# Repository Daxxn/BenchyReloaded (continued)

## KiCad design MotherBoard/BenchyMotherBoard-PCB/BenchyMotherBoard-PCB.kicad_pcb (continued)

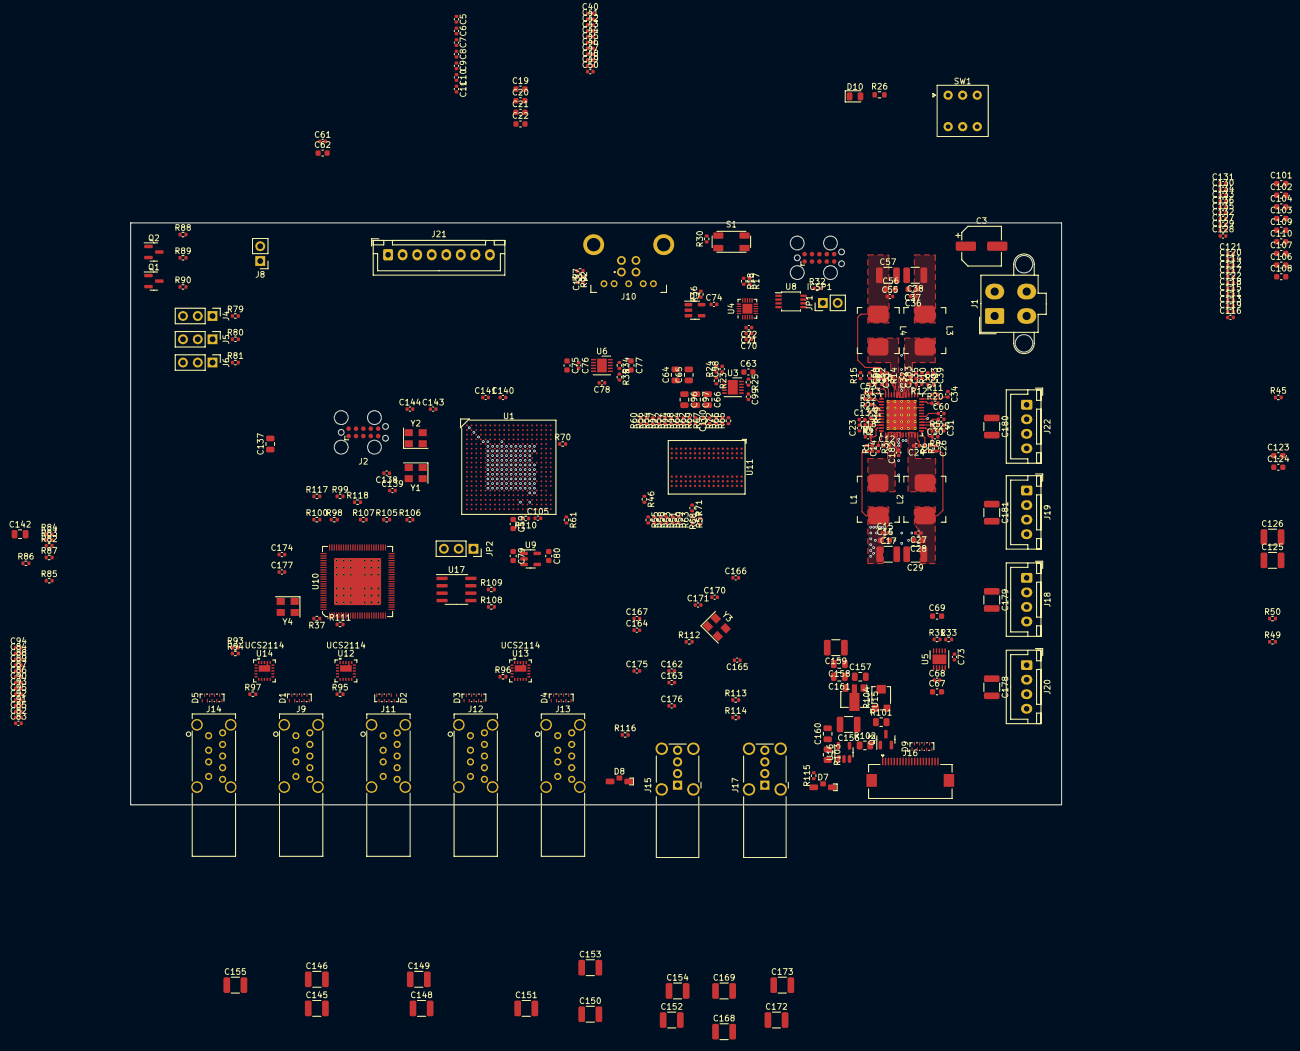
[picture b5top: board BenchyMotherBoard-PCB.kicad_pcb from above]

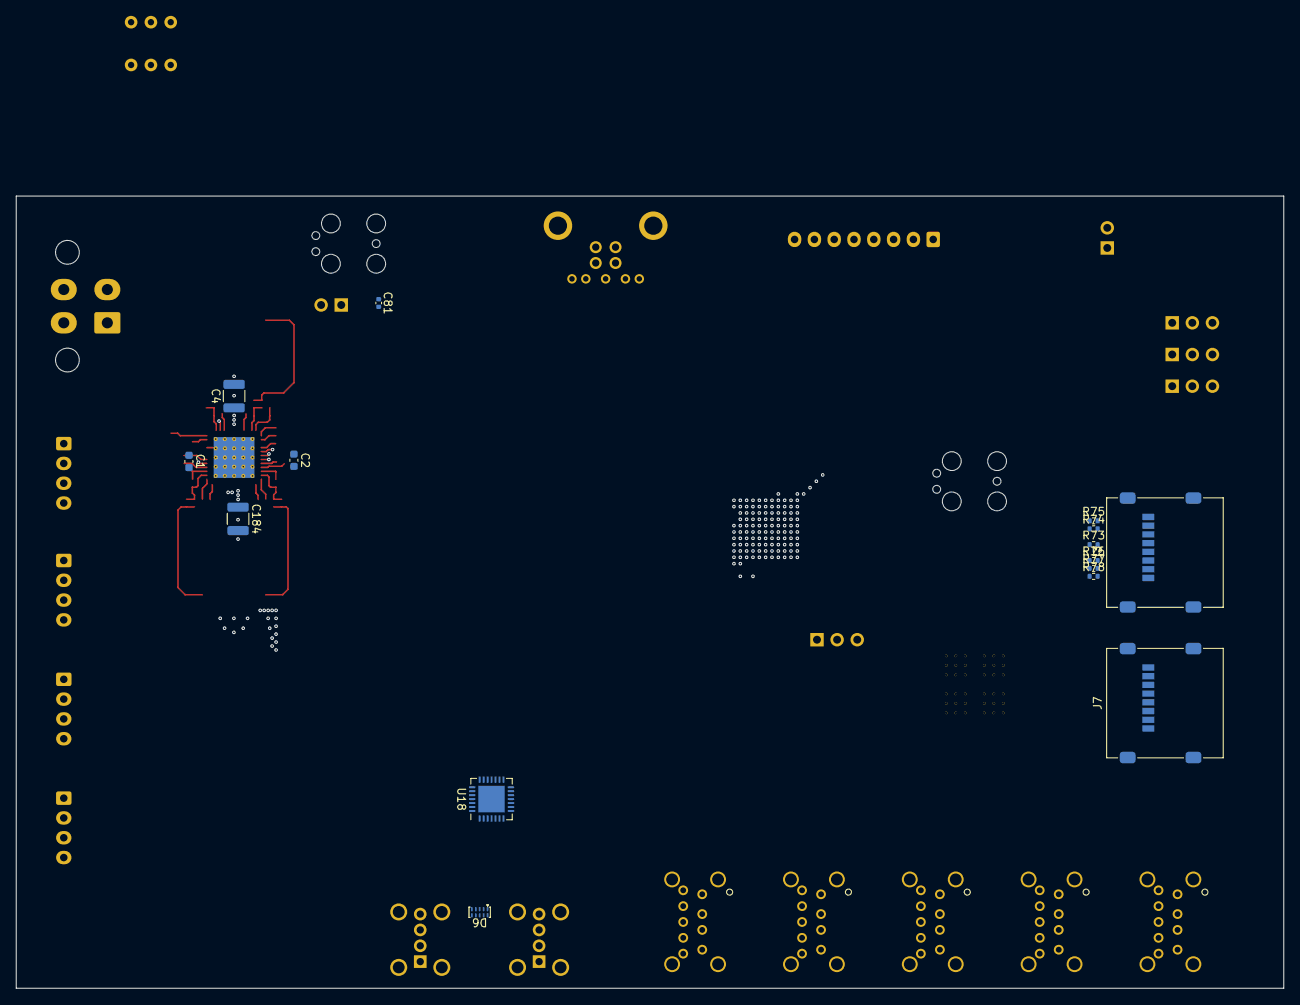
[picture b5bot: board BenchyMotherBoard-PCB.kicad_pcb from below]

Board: 8 copper layers, 160.0 x 100.0 mm, 360 parts (15 on the bottom side), 267 nets.

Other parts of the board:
kibuzzard-63F3F2E0: G***; kibuzzard-63F3F2E0

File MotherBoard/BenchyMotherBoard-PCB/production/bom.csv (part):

Designator,Footprint,Quantity,Value,LCSC Part #
C1,0603,1,100nF,
C10,0402,1,100nF,
C100,0402,1,100nF,
C101,0402,1,100nF,
C102,0402,1,100nF,
C103,0402,1,100nF,
C104,0402,1,100nF,
C105,0402,1,100nF,
C106,0402,1,100nF,
C107,0402,1,100nF,
C108,0402,1,100nF,
C109,0402,1,100nF,
C11,0402,1,100nF,
C110,0402,1,100nF,
C111,0402,1,100nF,
C112,0402,1,100nF,
C113,0402,1,100nF,
C114,0402,1,100nF,
C115,0402,1,100nF,
C116,0402,1,100nF,
C117,0402,1,100nF,
C118,0402,1,100nF,
C119,0402,1,100nF,
C12,0402,1,100nF,
C120,0402,1,100nF,
C121,0402,1,100nF,
C122,0402,1,100nF,
C123,0603,1,1uF,
C124,0603,1,1uF,
C125,1210,1,22uF,
C126,1210,1,22uF,
C127,0402,1,100nF,
C128,0402,1,100nF,
C129,0402,1,100nF,
C13,0402,1,100nF,
C130,0402,1,100nF,
C131,0402,1,100nF,
C132,0402,1,100nF,
C133,0402,1,100nF,
C134,0402,1,100nF,
C135,0402,1,100nF,
C136,0402,1,100nF,
C137,0805,1,4.7uF,
C138,0402,1,15pF,
C139,0402,1,15pF,
C14,0402,1,100nF,
C140,0402,1,1nF,
C141,0402,1,10nF,
C142,0805,1,4.7uF,
C143,0402,1,15pF,
C144,0402,1,15pF,
C145,1210,1,10uF,
C146,1210,1,10uF,
C147,0402,1,100nF,
C148,1210,1,10uF,
C149,1210,1,10uF,
C15,0402,1,100nF,
C150,1210,1,10uF,
C151,1210,1,10uF,
C152,1210,1,10uF,
C153,1210,1,10uF,
C154,1210,1,10uF,
C155,1210,1,10uF,
C156,1210,1,10uF,
C157,0805,1,1uF,
C158,0805,1,1uF,
C159,1210,1,10uF,
C16,0603,1,1uF,
C160,0805,1,1uF,
C161,0805,1,100nF,
C162,0402,1,100nF,
C163,0402,1,100nF,
C164,0402,1,100nF,
C165,0402,1,100nF,
C166,0402,1,100nF,
C167,0402,1,100nF,
C168,1210,1,10uF,
C169,1210,1,1uF,
C17,1210,1,10uF,
C170,0402,1,15pF,
C171,0402,1,15pF,
C172,1210,1,10uF,
C173,1210,1,1uF,
C174,0402,1,15pF,
C175,0402,1,100nF,
C176,0402,1,100nF,
C177,0402,1,15pF,
C178,1210,1,10uF,
C179,1210,1,10uF,
C18,0402,1,47pF,
C180,1210,1,10uF,
C181,1210,1,10uF,
C182,0402,1,100nF,
C183,0402,1,100nF,
C184,1210,1,10uF,
C185,0402,1,100nF,
C186,0402,1,100nF,
C187,0402,1,100nF,
C188,0402,1,100nF,
C189,0402,1,100nF,
C19,0603,1,1uF,
C190,0402,1,100nF,
C191,0402,1,100nF,
C192,0402,1,100nF,
C193,0402,1,100nF,
C194,0603,1,1uF,
C195,0402,1,100nF,
C2,0603,1,100nF,
C20,0603,1,1uF,
C21,0603,1,1uF,
C22,0603,1,1uF,
C23,0402,1,330pF,
C24,0402,1,100nF,
C25,0402,1,100nF,
C26,0402,1,100nF,
C27,0402,1,100nF,
C28,0603,1,1uF,
C29,1210,1,10uF,
C3,CP_Elec_6.3x7.7,1,47uF,
C30,0402,1,117pF,
C31,0402,1,1nF,
C32,0402,1,100nF,
C33,0402,1,100pF,
C34,0402,1,100nF,
C35,0402,1,100nF,
C36,0402,1,100nF,
C37,0603,1,1uF,
C38,1210,1,10uF,
C39,0402,1,820pF,
C4,1210,1,10uF,
C40,0402,1,100nF,
C41,0402,1,100nF,
C42,0402,1,100nF,
C43,0402,1,100nF,
C44,0402,1,100nF,
C45,0402,1,100nF,
C46,0402,1,100nF,
C47,0402,1,100nF,
C48,0402,1,100nF,
C49,0402,1,100nF,
C5,0402,1,100nF,
C50,0402,1,100nF,
C51,0402,1,100nF,
C52,0402,1,150pF,
C53,0402,1,100nF,
C54,0402,1,100nF,
C55,0402,1,100nF,
C56,0603,1,1uF,
C57,1210,1,10uF,
C58,0402,1,1.5nF,
C59,0603,1,2.2uF,
C6,0402,1,100nF,
C60,0402,1,100nF,
C61,0603,1,2.2uF,
C62,0603,1,1uF,
C63,0603,1,4.7uF,
C64,0805,1,10uF,
C65,0805,1,10uF,
C66,0805,1,10uF,
C67,0402,1,100nF,
C68,0402,1,100nF,
C69,0603,1,2.2uF,
C7,0402,1,100nF,
C70,0603,1,1uF,
C71,0402,1,100nF,
C72,0402,1,100nF,
C73,0603,1,1uF,
C74,0402,1,100nF,
C75,0603,1,1uF,
C76,0402,1,100nF,
C77,0603,1,4.7uF,
C78,0402,1,200nF,
C79,0603,1,1uF,
C8,0402,1,100nF,
C80,0603,1,1uF,
C81,0402,1,100nF,
C82,0402,1,100nF,
C83,0402,1,100nF,
C84,0402,1,100nF,
C85,0402,1,100nF,
C86,0402,1,100nF,
C87,0402,1,100nF,
C88,0402,1,100nF,
C89,0402,1,100nF,
C9,0402,1,100nF,
C90,0402,1,100nF,
C91,0402,1,100nF,
C92,0402,1,100nF,
C93,0402,1,100nF,
C94,0402,1,100nF,
C95,0402,1,100nF,
C96,0805,1,10uF,
C97,0805,1,10uF,
C98,0402,1,1nF,
C99,0402,1,100nF,
"D1, D2, D3, D4, D5, D9",U-DFN3810-9,6,ESDLC5V0PB8,
D10,0805,1,GREEN,
D11,0805,1,RED,
D12,0805,1,ORANGE,
D13,0805,1,RED,
D14,0805,1,ORANGE,
D15,0805,1,GREEN,
D6,DFN2510A-10,1,PUSB3AB4-2USB,
D7,LED-SMD-1204_RA,1,ORANGE,
D8,LED-SMD-1204_RA,1,YELLOW,
"H1, H2, H3, H4",MountingHole_3.5mm_Pad_Via,4,M3,
"H10, H5, H6, H7, H8, H9",MountingHole_2.2mm_M2_ISO7380_Pad,6,M2,
ICSP1,Tag-Connect_TC2050-IDC-FP_2x05_P1.27mm_Vertical,1,ICSP,
J1,4-Pin_Molex_Mini-Fit_Jr_Vertical_Mount,1,PWR-CONN,
J10,USB-GSB3211311WEU,1,USB3_B,
J11,GSB4116341HR,1,USB3-PORT2,
J12,GSB4116341HR,1,USB3-PORT3,
J13,GSB4116341HR,1,USB3-PORT4,
J14,GSB4116341HR,1,USB3-PORT5,
J15,1002-014-01000,1,USB-INTERNAL-PORT1,
J16,FH12A-20S-0.5SH55,1,TFT-DISPLAY,
J17,1002-014-01000,1,USB-INTERNAL-PORT2,
J18,JST_XH_B4B-XH-A_Vertical,1,COMMS-PWR,
J19,JST_XH_B4B-XH-A_Vertical,1,COMMS-ELOAD,
J2,Tag-Connect_TC2050-IDC-FP_2x05_P1.27mm_Vertical,1,SWD-TAG,
J20,JST_XH_B4B-XH-A_Vertical,1,COMMS-SWITCHER,
J21,JST_XH_B8B-XH-A_1x08_P2.50mm_Vertical,1,RELAYS-CONN,
J22,JST_XH_B4B-XH-A_Vertical,1,COMMS-LOGIC,
J3,microSD_HC_Molex_47219-2001,1,FILES-SD-CARD,
J7,microSD_HC_Molex_47219-2001,1,BOOT-SD-CARD,
J8,PinHeader_1x02_P2.54mm_Vertical,1,FAN-CONN,
J9,GSB4116341HR,1,USB3-PORT1,
JP1,PinHeader_1x02_P2.54mm_Vertical,1,PWR-ICSP-RST,
JP2,PinSocket_1x03_P2.54mm_Vertical,1,WP-JMP,
L1,PA4341,1,22uH,
"L2, L3, L4",PA4341,3,10uH,
Q1,SOT-23,1,SQ2310ES_SOT23,
Q2,SOT-23,1,MMBT2222A,
Q3,SOT-23,1,RQ5A030AP,
R1,0402,1,24K,
R10,0402,1,13K,
R100,0402,1,10K,
R101,0805,1,10 1%,
R102,0805,1,120,
R103,0805,1,330,
R104,Bourns_TC33X,1,10K,
R105,0402,1,10K,
R106,0402,1,200K,
R107,0402,1,200K,
R108,0402,1,2.2K,
R109,0402,1,2.2K,
R11,0402,1,10K,
R110,0402,1,3K,
R111,0402,1,10K,
R112,0402,1,12K 1%,
R113,0402,1,50K,
R114,0402,1,50K,
R115,0402,1,1K,
R116,0402,1,1K,
R117,0402,1,10K,
R118,0402,1,200K,
R119,0402,1,4.7K,
R12,0402,1,15K,
R13,0402,1,8.2K,
R14,0402,1,4.3K,
R15,0402,1,10K,
R16,0402,1,11K,
R17,0402,1,2.2K,
R18,0402,1,2.2K,
R19,0402,1,10K,
R2,0402,1,24K,
R20,0402,1,10K,
R21,0402,1,160K,
R22,0402,1,160K,
R23,0402,1,10K,
R24,0402,1,10K,
R25,0402,1,10K,
R26,0603,1,500,
R27,0402,1,1K,
R28,0402,1,1K,
R29,0402,1,1K,
R3,0402,1,10K,
R30,0402,1,10K,
R31,0603,1,500,
R32,0402,1,10K,
R33,0603,1,500,
R34,0402,1,10K,
R35,0402,1,6.8K,
R36,0402,1,1K,
R37,0402,1,12K 1%,
R38,0603,1,500,
R39,0603,1,500,
R4,0402,1,7.5K,
R40,0603,1,500,
R41,0402,1,10K,
R42,0402,1,100,
R43,0402,1,10K,
R44,0402,1,56,
R45,0402,1,100,
R46,0402,1,56,
R47,0402,1,56,
R48,0402,1,56,
R49,0402,1,10K,
R5,0402,1,10K,
R50,0402,1,10K,
R51,0402,1,56,
R52,0402,1,56,
R53,0402,1,56,
R54,0402,1,56,
R55,0402,1,56,
R56,0402,1,56,
R57,0402,1,56,
R58,0402,1,56,
R59,0402,1,56,
R6,0402,1,6.2K,
R60,0402,1,56,
R61,0402,1,56,
R62,0402,1,56,
R63,0402,1,56,
R64,0402,1,56,
R65,0402,1,56,
R66,0402,1,56,
R67,0402,1,56,
R68,0402,1,56,
R69,0402,1,56,
R7,0402,1,10K,
R70,0402,1,240 1%,
R71,0402,1,240 1%,
R72,0402,1,56,
R73,0402,1,10K,
R74,0402,1,47K,
R75,0402,1,47K,
R76,0402,1,47K,
R77,0402,1,47K,
R78,0402,1,47K,
R79,0402,1,100,
R8,0402,1,10K,
R80,0402,1,100,
R81,0402,1,100,
R82,0402,1,10K,
R83,0402,1,47K,
R84,0402,1,47K,
R85,0402,1,47K,
R86,0402,1,47K,
R87,0402,1,47K,
R88,0402,1,10K,
R89,0402,1,100,
R9,0402,1,10K,
R90,0402,1,1K,
R91,0402,1,43K,
R92,0402,1,50K,
R93,0402,1,2.2K,
R94,0402,1,2.2K,
R95,0402,1,18K,
R96,0402,1,18K,
R97,0402,1,18K,
R98,0402,1,10K,
R99,0402,1,10K,
S1,TL1105SF,1,PWR-SW,
S2,TL3365AF180QG,1,PWR-RESET,
SW1,SW_DIP_SPSTx03_Slide_Copal_CVS-03xB_W5.9mm_P1mm,1,BOOT-SEL,
TP1,TestPoint_Pad_D1.5mm,1,TP-VDD-CORE,
TP10,TestPoint_Pad_D1.5mm,1,TP-1V1-REG,
TP11,TestPoint_Pad_D1.5mm,1,TP-1V8-REG,
TP12,TestPoint_Pad_D1.5mm,1,TP-DSI-REG,
TP2,TestPoint_Pad_D1.5mm,1,TP-VDD-DDR,
TP3,TestPoint_Pad_D1.5mm,1,TP-VDD,
TP4,TestPoint_Pad_D1.5mm,1,TP-USB-CORE,
TP5,TestPoint_Pad_D1.5mm,1,TP-VTT,
TP6,TestPoint_Pad_D1.5mm,1,TP-VREF-DDR,
TP7,TestPoint_Pad_D1.5mm,1,TP-VDDA,
TP8,TestPoint_Pad_D1.5mm,1,TP-VDD-USB,
TP9,TestPoint_Pad_D1.5mm,1,TP-VDD-PWR,
U1,LFBGA354-P0.8mm,1,STM32MP157FAB1,
U10,100-VQFN-GND_12X12,1,USB7206C,
U11,DDR_FBGA-96_9x13mm_P0.8mm,1,IS43TR16256B-125KBLI,
"U12, U13, U14",UCS2114T-1-V_LXVAO-Custom,3,UCS2114,
U15,SOT-89-3,1,LM317L,
U16,SOT-23-5,1,AS321,
U17,SOIC-8_3.9x4.9mm_P1.27mm,1,24LC08,
U18,QFN-28-1EP_5x5mm_P0.5mm_EP3.35x3.35mm,1,USB2412,
U2,QFN-48-1EP_7x7mm_P0.5mm_EP5.15x5.15mm_ThermalVias,1,TPS65400RGZT,
U3,DFN-10-1EP_3x3mm_P0.5mm_EP1.65x2.38mm,1,NCP51200,
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
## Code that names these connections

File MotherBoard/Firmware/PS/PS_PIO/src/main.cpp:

#include <Arduino.h>
#include <Wire.h>
#include "PMBus.h"

const int PWR_ON_RST_PIN =  PIN_PA4;
const int PWR_ON =  PIN_PA5;
const int PMBUS_ALERT_PIN = PIN_PA6;
const int PWR_SW_PIN = PIN_PA7;

const int ALL_GOOD_PIN = PIN_PB4;
const int PERIPH_EN_PIN = PIN_PB5;
const int PWR_ERR_PIN = PIN_PC0;
const int USB_EN_PIN = PIN_PC1;
const int DDR_EN_PIN = PIN_PC2;
const int VDDA_EN_PIN = PIN_PC3;

const uint8_t PMBusAddress = 0x6F;

PMBusState state = PMBusState();
PMBus pmBus = PMBus(PMBUS_ALERT_PIN, PMBusAddress);

// Power switch state for MPU
bool btnPrev = false;
bool powerON = false;

void InitPins()
{
  // PORTA_DIRSET   = 0;
  // PORTB_DIRSET   = 0b00100000;
  // PORTC_DIRSET   = 0b00001111;
  // // PORTC_PIN0CTRL = 0b10000000;

  // PORTB_OUT = 0;
  // PORTC_OUT = 0;

  pinMode(PWR_ON_RST_PIN, INPUT);
  pinMode(PWR_ON, INPUT);
  pinMode(PWR_SW_PIN, INPUT);
  pinMode(ALL_GOOD_PIN, INPUT);
  pinMode(PERIPH_EN_PIN, OUTPUT);
  pinMode(PWR_ERR_PIN, OUTPUT);
  pinMode(USB_EN_PIN, OUTPUT);
  pinMode(DDR_EN_PIN, OUTPUT);
  pinMode(VDDA_EN_PIN, OUTPUT);
}

void WriteSettings()
{
  // pmBus.SoftReset();
  delay(1000);
  // pmBus.SetEnablePins(PM_ENABLE_CONFIG::ALL_ACTIVE);

  // pmBus.WriteAllSettings();

  // uint8_t startSeq[4] = {1, 2, 3, 3};
  // uint8_t stopSeq[4] = {3, 3, 2, 1};
  // pmBus.SetSequences(startSeq, stopSeq);

  // pmBus.SetWriteProtection(PM_WRITE_PROTECT::ALL_ENABLE);
  // pmBus.SetEnablePins(PM_ENABLE_CONFIG::ALL_INACTIVE);
  #ifdef WRITE_SETTINGS
  pmBus.WriteAllSettings(true);
  #else
  pmBus.WriteAllSettings(false);
  #endif
}

void PinStartupSeq()
{
  digitalWrite(DDR_EN_PIN, HIGH);
  digitalWrite(USB_EN_PIN, HIGH);
}

void Blink(int count)
{
  for (size_t i = 0; i < count; i++)
  {
    // PORTC_OUTSET = 1;
    digitalWrite(PWR_ERR_PIN, HIGH);
    delay(100);
    // PORTC_OUTCLR = 1;
    digitalWrite(PWR_ERR_PIN, LOW);
    delay(100);
  }
}

void setup() {
  InitPins();
  digitalWrite(PWR_ERR_PIN, HIGH);
  state.EnableConfig = PM_ENABLE_CONFIG::ALL_INACTIVE;
  // state.SequenceConfig = PM_SEQUENCE_CONFIG::INGORE_PGOOD;
  state.Rails[0] = RailStatus(); // VDD
  state.Rails[1] = RailStatus(); // VDD-CORE
  state.Rails[2] = RailStatus(); // VDD-DDR
  state.Rails[3] = RailStatus(); // USB-CORE
  state.Rails[0].Sequence.Set(0, 3);
  state.Rails[1].Sequence.Set(1, 2);
  state.Rails[2].Sequence.Set(2, 1);
  state.Rails[3].Sequence.Set(3, 0);
  #ifdef MAN
  state.Rails[0].Delay.Set(0, 100);
  state.Rails[1].Delay.Set(100, 100);
  state.Rails[2].Delay.Set(100, 100);
  state.Rails[3].Delay.Set(100, 0);
  #else
  state.Rails[0].Delay.Set(0, 0b100);
  state.Rails[1].Delay.Set(0b010, 0b010);
  state.Rails[2].Delay.Set(0b100, 0b100);
  state.Rails[3].Delay.Set(0b100, 0);
  #endif
  // Serial.begin(115200);
  pmBus.Init(&state);
  // #ifdef MAN
  // if(powerON)
  // {
  //   pmBus.ManualSequence(PM_RAIL_STATE::ENABLE);
  // }
  // #else
  // #endif
  WriteSettings();
  digitalWrite(VDDA_EN_PIN, HIGH);
  delay(100);
  digitalWrite(PWR_ERR_PIN, LOW);
  digitalWrite(DDR_EN_PIN, HIGH);
}

void loop() {
  #ifndef MAN
  // Blink(2);
  digitalWrite(PWR_ERR_PIN, HIGH);
  // digitalWrite(USB_EN_PIN, HIGH);
  pmBus.EnableAllRails();
  // delay(1000);
  digitalWrite(PWR_ERR_PIN, LOW);
  delay(5000);
  // digitalWrite(USB_EN_PIN, LOW);
  pmBus.DisableAllRails();
  Blink(4);

  // delay(4000);
  // pmBus.ReadStatus(0);
  // pmBus.ReadRailPGOODs();
  // Blink(pmBus.GetPGoods());

  delay(5000);
  #else
  // Blink(4);
  uint8_t btn = digitalRead(PWR_SW_PIN);
  if (btn == LOW && btn != btnPrev)
  {
    powerON = !powerON;
    btnPrev = btn;
    pmBus.ManualSequence(powerON ? PM_RAIL_STATE::ENABLE : PM_RAIL_STATE::DISABLE);
    delay(150);
    Blink(4);
  }
  #endif
}

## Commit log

2023-02-18 initial Commit - Add mother MPU and PWR ICs
2023-02-19 Add MORE regulators, USB, Display, and SDCard
2023-02-20 Initial schematic lock
2023-02-20 (WIP) Start layout
2023-02-21 (WIP) Replaced DDR VRef with reg and started layout
2023-02-23 Add PGOOD led and replace PWR switch
2023-02-24 Start DDR3 layout
2023-02-25 DDR memory length match (Hopefully)
2023-02-26 (WIP) DDR memory length match (re-calc)
2023-02-27 Finish DDR3 memory layout
2023-02-28 Mostly routed USB
2023-03-01 Most routing completed
2023-03-02 Fix power reset and finish routing
2023-03-02 (WIP) Fixing stripline impedance for DDR memory
2023-03-04 Remove old DDR traces, start rerouting
2023-03-05 Initial DDR routing, start fixing skew
2023-03-05 Replace USB TVS W/ custom & finish DDR data layout
2023-03-05 DDR layout mostly complete
2023-03-07 REV1 - Finish layout and finalize pcb
2023-03-07 REV1 - Finish layout and generate gerbers (add lfs ext for PCB)
2023-03-07 Fix file size issue with custom PCB fonts
2023-03-07 test
2023-03-10 Fix fab layer text and generate BOM
2023-03-10 Fix power stuff
2023-03-12 Add volt meter PCB
2023-03-23 Add voltmeter PCB
2023-03-23 Fix schematic bugs and add PIO firmware (Not Working)
2023-03-24 Add mplab config and proj / remove pio proj
2023-03-26 Fix issues with power supply schematic
2023-03-27 Add extra functions to PMBus and create manual power sequence
2023-03-27 Add USB power connector and start layout fixes
2023-03-27 Finish trace layout and update PS fb resistor values
2023-05-13 Wrap up REV2 and add voltmeter gerbers
2023-05-14 (!!WIP!!) Started schematic and block diagram
2023-06-02 (WIP) Added PS supervisor
2023-06-03 (WIP) Finish more of the PS schematic
2023-06-03 (WIP) More work on power supply sequencing
2023-06-05 (WIP) Complete most of the PS and boot schematics
2023-06-09 Add new ethernet chip - KSZ9031
2023-06-11 (WIP) Almost done with schematic
2023-06-12 Start PCB layout
2023-06-13 Fix power net names and increase PCB size
2023-06-15 (WIP) Still laying out PCB
2023-09-28 Update README.md
    Fix alot of the changes made with the new version of Benchy.
2023-09-28 Add docs for benchy reloaded
2023-09-28 Remove un-archived step files
2023-09-28 Update gitignore
2023-09-28 Update readme and add new renders
2023-09-28 Update readme again
2025-04-12 Replacing motherboard and more - SAVE
2025-04-13 Schematic capture mostly complete. Starting PCB layout
